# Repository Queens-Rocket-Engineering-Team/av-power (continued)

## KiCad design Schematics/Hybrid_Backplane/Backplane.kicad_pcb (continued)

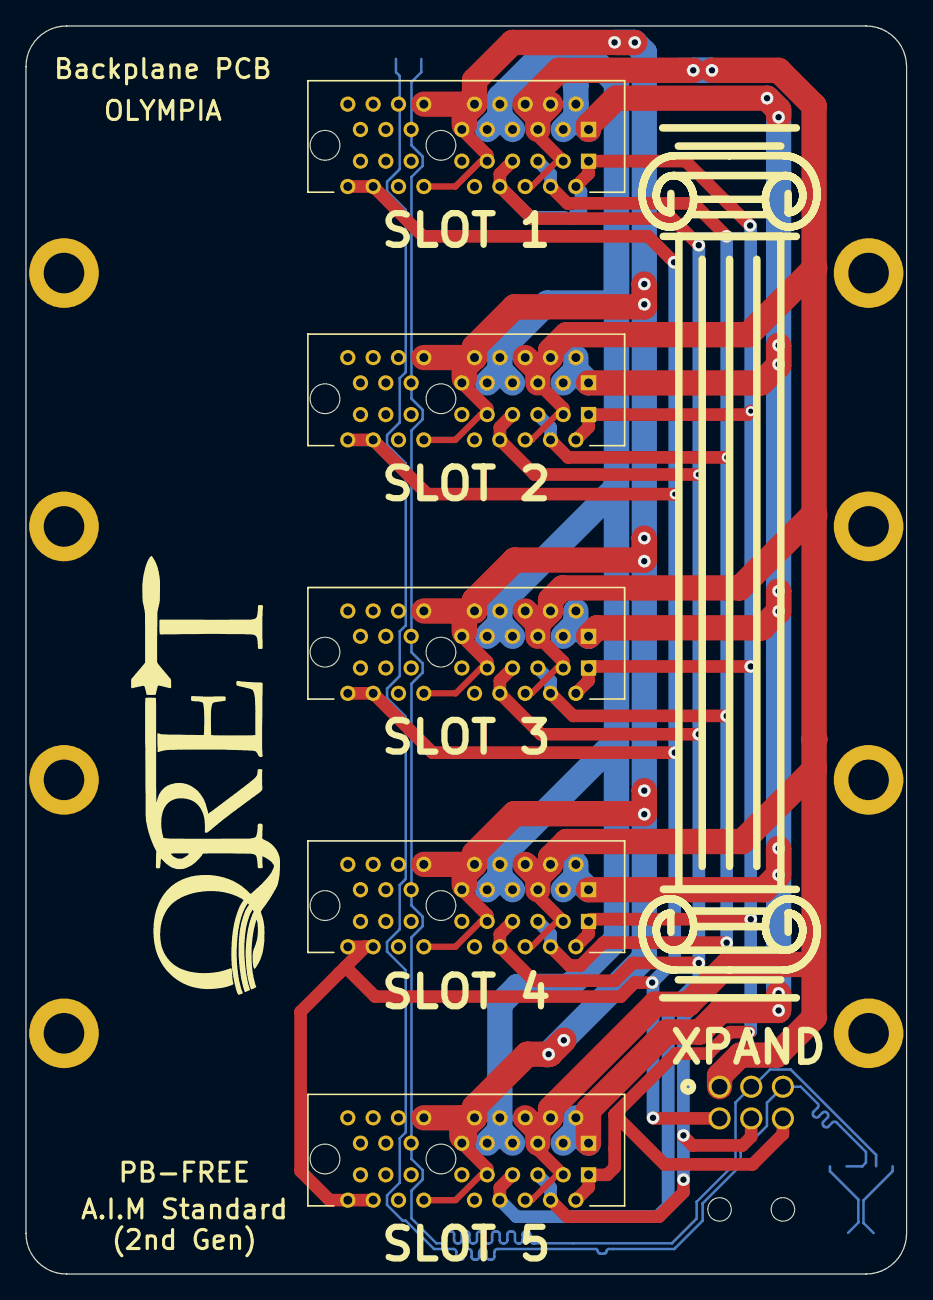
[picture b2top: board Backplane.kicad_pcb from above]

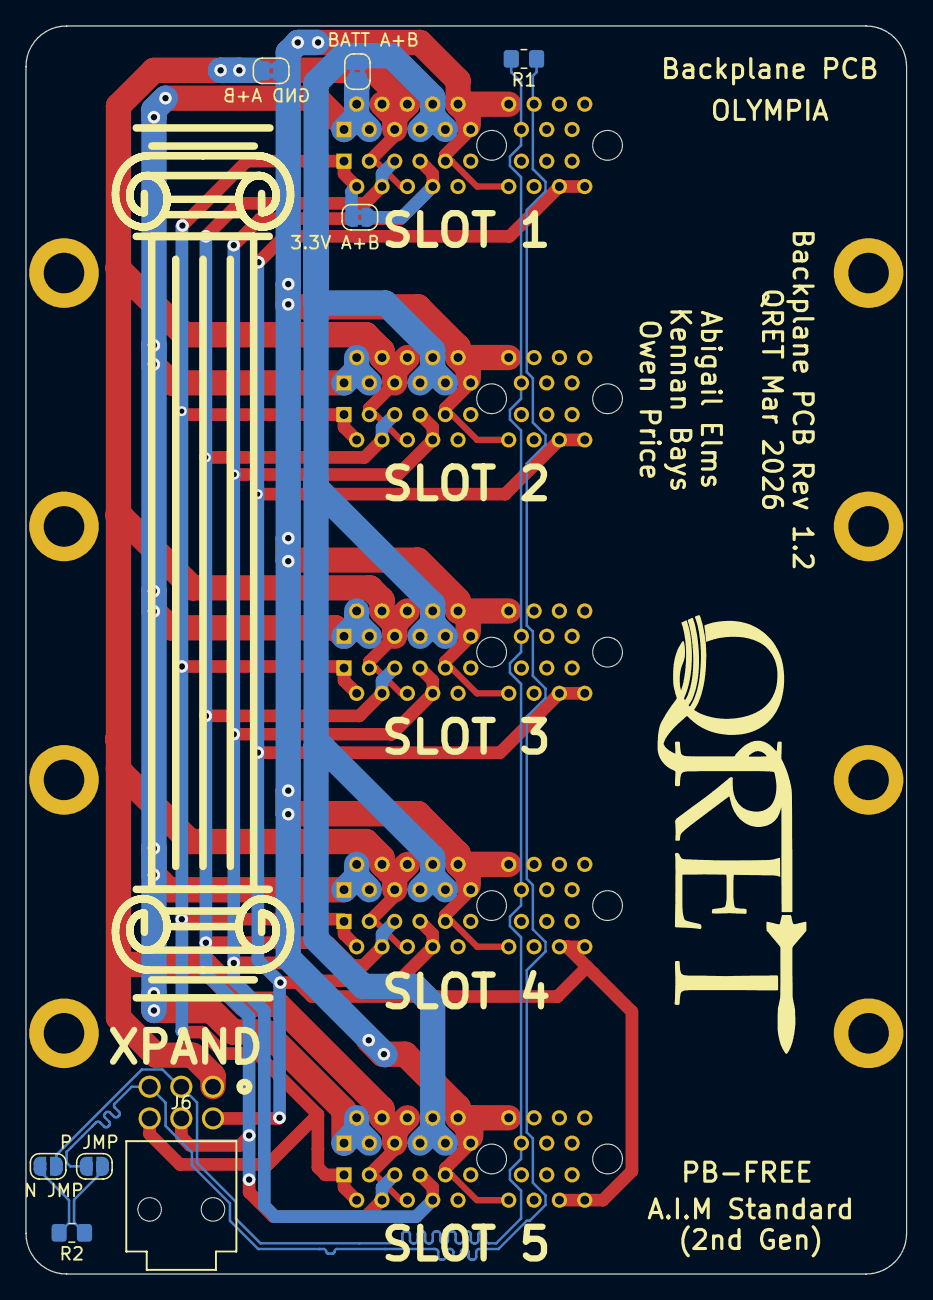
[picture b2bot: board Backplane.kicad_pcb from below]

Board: 2 copper layers, 69.5 x 98.5 mm, 21 parts (8 on the bottom side), 12 nets.

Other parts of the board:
H5, H6, H7, H8: MountingHole; MountingHole_3.2mm_M3_ISO14580_Pad

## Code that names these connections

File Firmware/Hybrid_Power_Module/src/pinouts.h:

#ifndef PINOUTS_H
#define PINOUTS_H

#include <Arduino.h> // needed for PB/A# pin assignment
#include <cstdint>

// pinouts.h - APOLLO Hybrid Power Module V1.0 2025/2026 (STM32F103CBT6) pin map.
namespace pins {

// --- Serial (USB-UART Bridge; TX/RX are swapped on the PCB) ---
//  !!! Fix in next board spin !!!
//  Use software serial
constexpr uint8_t kSerialTx = PB10; // USART_TX -> USB_RX
constexpr uint8_t kSerialRx = PB11; // USART_RX <- USB_TX

// --- CAN bus ---
constexpr uint8_t kCanRx = PB8;
constexpr uint8_t kCanTx = PB9;

// --- Flash interface (SPI) ---
constexpr uint8_t kFlashReset = PB12;
constexpr uint8_t kSpiSclk   = PB13;
constexpr uint8_t kSpiMiso   = PB14;
constexpr uint8_t kSpiMosi   = PB15;

// --- Voltage and current sensing ---
constexpr uint8_t kBatterySense    = PA0;
constexpr uint8_t kGseSense        = PB1;
constexpr uint8_t k24VCurrentSense = PB0;
constexpr uint8_t k5VSense         = PA1;
// Power enable for 3.3v current sense
constexpr uint8_t k3V3AcsPower     = PA4;
constexpr uint8_t k3V3CurrentSense = PA2;
// Power enable for 5v current sense
// !!! DO NOT POWER ON (using wrong current sense could break mcu)
constexpr uint8_t k5VAcsPower      = PA6;
constexpr uint8_t k5VCurrentSense  = PA5;

// --- LEDs ---
constexpr uint8_t kDebugLed = PA7;

}

#endif // PINOUTS_H

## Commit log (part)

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2026-01-07 Cleanup of branch for importing into dedicated repo - dedicated for power deliver systems - added direct local paths to datasheets in schematic - added all datasheets related to projects
2026-02-04 init commit of hybrid backplane with new extension connector - using bridges to merge POWER trace B with A for altimter - add 120ohm termination bridge to allow CAN to work standlone
2026-02-04 Current Updated Backplance
    Did the wiring for the PCB. Not sure how to properly connect the edge connectors to the new connector (they don't want to connect)
2026-02-09 init commit of power board hybrid revision
2026-02-09 updated backplane length to fit in stack design - need to route traces to extension connector
2026-02-21 init commit of power design, with Bucks completed - started Boost design
2026-02-22 cleaned up boost pdf & lcsc and noted next steps
2026-02-22 adding power ORing circuit
2026-02-22 opted out of charger in design
2026-02-26 Backplane Trace
2026-03-02 start of my own backplane layout
2026-03-04 add equations for Boost and instructions for buck design changes
2026-03-04 fixed skew for CAN bus
2026-03-05 Update power.kicad_sch
    Changed frequency to 500 000Hz and updated schematics (not the new footprint)
2026-03-05 3.3V inductor changed to 27uF 3.6A
2026-03-05 Update buck designs for 500kHz, prioritize efficiency
2026-03-05 updated buck input caps voltage rating to 50V
2026-03-10 complete clamping and rpp for 24v gse source - chose 24v source ORing mosfet
2026-03-11 ongoing equation for boost calculations
2026-03-18 Reverted Commit
2026-03-18 Update Text
2026-03-19 finalized buck and boost designs,
2026-03-19 minor review of part numbers - NEED major review of buck and boost design
2026-03-20 started layout design - added shunt based 24V current sensing
2026-03-21 current progress on power board
2026-03-22 major layout progress, still need to place MCU
2026-03-23 continueing layout, confirmed all devices will fix - need to add bulk rail caps - fixed issue in oring logic
2026-03-23 New Backplane
2026-03-23 confirm layout, confirm everything fits
2026-03-24 completed all power traces, finalizing signal traces
2026-03-24 continuing to finish signal traces, added extra decouplping caps near PCIE
2026-03-25 finished all traces, confirmed major DRC errors - need to fix silkscreen - review needed and LCSC verification
2026-03-25 updated todo lists
2026-03-26 Made Minor Updates
    - Update Silk Screen to Reflect 2026 Year
    - Connected CAN_P Line to Connectors
    - Moved R2 Slightly Away from the Edge
    - Fixed DRC Error With J6
    Still To Do:
    - Name Board
2026-03-26 Forgot to save Resistor Move
2026-03-26 hybrid backplane ready for order
2026-03-26 hybrid power board, with preserved OG Power board - still hybrid still needs review and silkscreen
2026-03-27 fix part number and bom formation, update mostfet based on stock
2026-03-27 restored non hybrid backplane
2026-03-27 finished power board silkscreen, needs final review before approval
2026-03-28 minor updates to part numbers and silkscreen
2026-03-28 Rename backplane diretory for consitency
2026-03-28 fixed voltage divder for GSE 24v
2026-03-28 changed current sense and switched to bidirectional TVS for GSE power
2026-03-29 add nano connector for xpand, adjust routing
2026-03-30 final board submitted to cart
2026-03-30 minor fixes to silkscreen
2026-03-30 using copper poor for 5v and 3.3v buck sw
2026-04-01 Update project season in README
    Updated project season from 2023-2025 to 2023-2026.
2026-04-01 Rename readme.md to README.md
2026-06-14 feat(power): implement dynamic state/error reporting and battery telemetry
2026-06-15 av-power: wire Hybrid_Power_Module power-FET + voltage subjects (schema v2)
    Migrate to node.* convention and publish the new power-FET (PwrPtUcm,
    PwrSolLcm, PwrPtLcm) and voltage subjects from schema v2; pinouts and
    platformio updates.
2026-06-18 Hybrid_Power: pass nowMs into service()
    Match the updated AimNetwork::service(nowMs, state, errorBits) signature.
2026-06-21 Hybrid_Power: node convention cleanup and naming alignment
    Apply lowerCamelCase naming, explicit Job init, and static combinedHooks
    fix consistent with the other five nodes.
